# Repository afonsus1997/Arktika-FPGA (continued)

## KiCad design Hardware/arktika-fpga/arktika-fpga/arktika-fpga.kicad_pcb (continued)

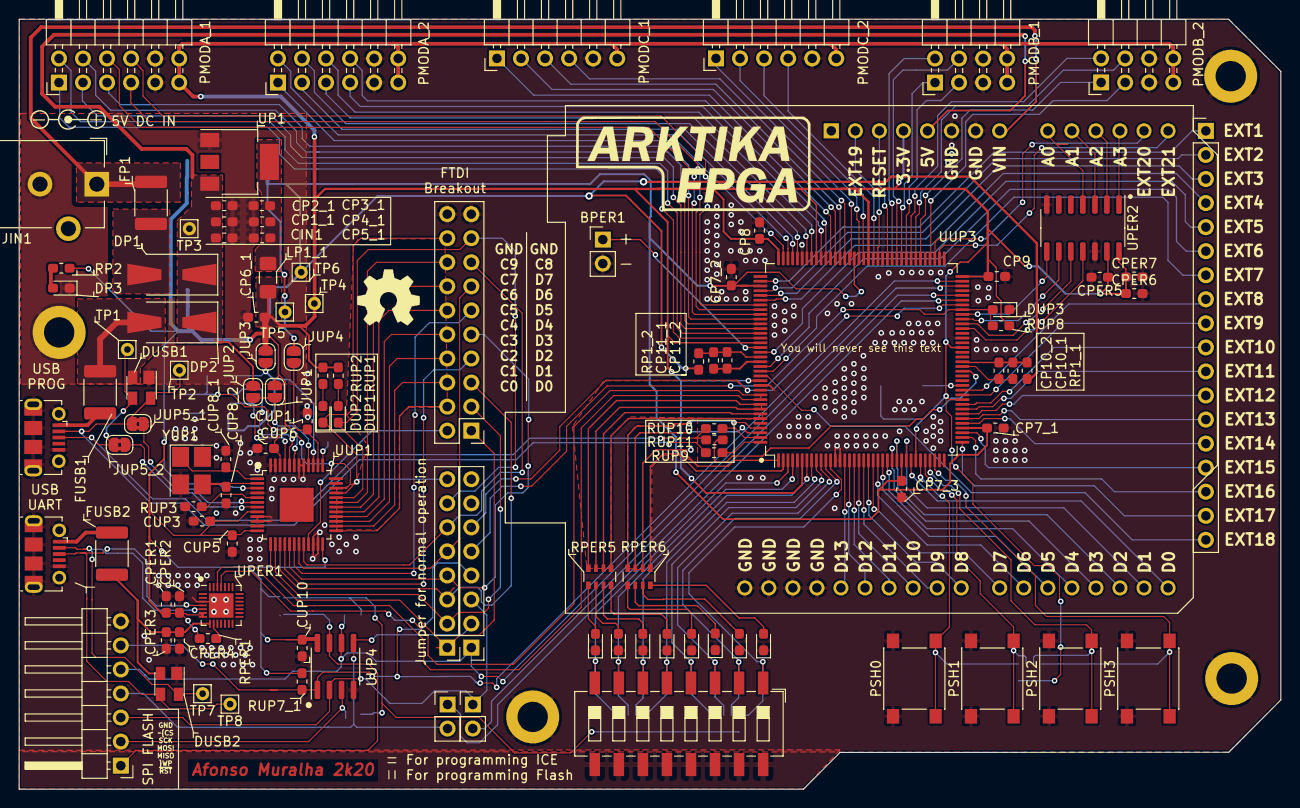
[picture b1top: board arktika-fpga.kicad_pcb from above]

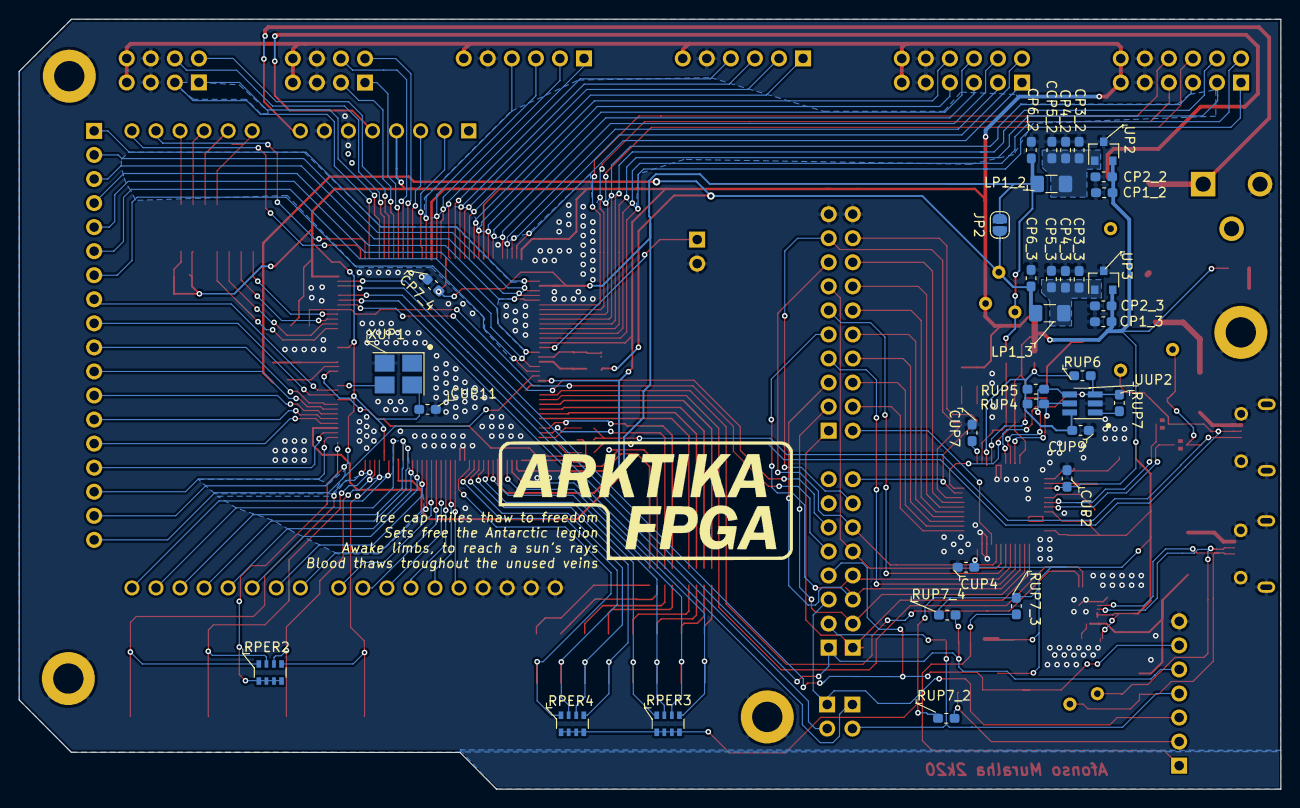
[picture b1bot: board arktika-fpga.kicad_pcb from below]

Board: 2 copper layers, 133.2 x 81.3 mm, 143 parts (35 on the bottom side), 178 nets.

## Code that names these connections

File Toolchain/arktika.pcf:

#Board Dedicated Oscillator
set_io --warn-no-port CLK 49

#=======Board LEDs========
set_io --warn-no-port LED0 2
set_io --warn-no-port LED1 1
set_io --warn-no-port LED2 142
set_io --warn-no-port LED3 141
set_io --warn-no-port LED4 139
set_io --warn-no-port LED5 138
set_io --warn-no-port LED6 137
set_io --warn-no-port LED7 136

set_io --warn-no-port led[0] 2
set_io --warn-no-port led[1] 1
set_io --warn-no-port led[2] 142
set_io --warn-no-port led[3] 141
set_io --warn-no-port led[4] 139
set_io --warn-no-port led[5] 138
set_io --warn-no-port led[6] 137
set_io --warn-no-port led[7] 136


#========Board Switches========
set_io --warn-no-port SW0 12
set_io --warn-no-port SW1 11
set_io --warn-no-port SW2 10
set_io --warn-no-port SW3 9
set_io --warn-no-port SW4 8
set_io --warn-no-port SW5 7
set_io --warn-no-port SW6 4
set_io --warn-no-port SW7 3

set_io --warn-no-port sw[0] 12
set_io --warn-no-port sw[1] 11
set_io --warn-no-port sw[2] 10
set_io --warn-no-port sw[3] 9
set_io --warn-no-port sw[4] 8
set_io --warn-no-port sw[5] 7
set_io --warn-no-port sw[6] 4
set_io --warn-no-port sw[7] 3


#========Board Push Buttons========
set_io --warn-no-port PSH0 31
set_io --warn-no-port PSH1 32
set_io --warn-no-port PSH2 33
set_io --warn-no-port PSH3 34

set_io --warn-no-port psh[0] 31
set_io --warn-no-port psh[1] 32
set_io --warn-no-port psh[2] 33
set_io --warn-no-port psh[3] 34

#========Board EXT Header========
set_io --warn-no-port EXT1 110
set_io --warn-no-port EXT2 112
set_io --warn-no-port EXT3 113
set_io --warn-no-port EXT4 114
set_io --warn-no-port EXT5 125
set_io --warn-no-port EXT6 128
set_io --warn-no-port EXT7 129
set_io --warn-no-port EXT8 48
set_io --warn-no-port EXT9 47
set_io --warn-no-port EXT10 45
set_io --warn-no-port EXT11 44
set_io --warn-no-port EXT12 43
set_io --warn-no-port EXT13 42
set_io --warn-no-port EXT14 41
set_io --warn-no-port EXT15 39
set_io --warn-no-port EXT16 38
set_io --warn-no-port EXT17 37
set_io --warn-no-port EXT18 130

 
#========Board Arduino Headers========
set_io --warn-no-port D0 29
set_io --warn-no-port D1 28
set_io --warn-no-port D2 26
set_io --warn-no-port D3 25
set_io --warn-no-port D4 24
set_io --warn-no-port D5 23
set_io --warn-no-port D6 22
set_io --warn-no-port D7 21
set_io --warn-no-port D8 20
set_io --warn-no-port D9 19
set_io --warn-no-port D10 18
set_io --warn-no-port D11 17
set_io --warn-no-port D12 16
set_io --warn-no-port D13 15

set_io --warn-no-port ARDUINO_RESET 85 
set_io --warn-no-port EXTRA1 87
set_io --warn-no-port EXTRA2 74
set_io --warn-no-port EXTRA3 75


#========Board Buzzer Header======== 
set_io --warn-no-port BUZZER 124 


#========Board ADC Pins========
set_io --warn-no-port ADC_CLK 61
set_io --warn-no-port ADC_MISO 62
set_io --warn-no-port ADC_MOSI 63
set_io --warn-no-port ADC_CS 64

#========Board USB Pins========
set_io --warn-no-port USBP 143
set_io --warn-no-port USBP2 52
set_io --warn-no-port USBN 144
set_io --warn-no-port UART_TX 135
set_io --warn-no-port UART_RX 134


#========Board PMOD Headers========
#TODO

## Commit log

2020-07-25 Updated to readme, initial hardware files
2020-07-25 Minor updates, added component search doc for development purposes
2020-07-25 Redid the kicad project. Last one was a mess
2020-07-25 Added more docs do readme, did board power
2020-07-26 Started doing usb and programming
2020-07-26 Added configuration for power regulation and programming nets
2020-07-26 Added misc components to the usb and prog schematic
2020-07-28 Added designators, some io, and some peripherals
2020-07-28 Assigned some footprints to components
2020-07-29 Minor fixes
2020-07-29 Minor fixes on fpga peripherals
2020-07-29 JNC: Updated component search doc with component list and datasheet links
2020-07-30 Minor fixes, added peripheral buses, added annotations and added crystal datasheets
2020-07-30 Added alternate power intput. Update some designators. Added fpga crystal
2020-07-30 Added fuse to usb peripheral, other minor changes
2020-07-30 Forgot to change fusb2 designator
2020-07-30 Updated eeprom info in component search, added missing bp cap to eeprom
2020-07-30 Misc changes and fixes
2020-07-31 Addded new hybrid crystal footprint, fixed missing footprints, created layout file for testing
2020-07-31 Added fuses library to project. Minor changes
2020-07-31 Added rescue files
2020-08-01 Misc schematic changes. Preliminary layout almost complete
2020-08-02 Major routing updates. Did work on silkscreen. Optimized io placing. Misc changes
2020-08-02 Added more IO
2020-08-02 Finished routing, did gnd planes, added more silkscreen and some manual via stitching. Pre-final layout.
2020-08-03 Minor layout fixes
2020-08-03 Fixed minor drc errors. removed usb jumpers and added needed resistors
2020-08-03 Minor layout changes
2020-08-04 Added silkscreen art and added media folder with the same art
2020-08-04 Minor layout fixes. Added new micro usb connector footprint and link. Misc silk changes
2020-08-04 Added pcbway logo to top silkscreen
2020-08-04 misc changes, exported test gerbers
2020-08-05 Exported final gerbers. Sent to fab
2020-08-06 Fixed clearance error on design. Sent to fab
2020-08-07 Fixed gerber format issue with manufacturer
2020-08-11 Added initial files for the toolchain information. Added basic example. Added pcf board file
2020-08-24 Generated gerbers without pcbway branding. Sent do fab
2020-09-22 exported schematics pdf
2020-09-27 Updated readme and added renders
2020-09-28 Fixed flash CS net
2020-09-28 Edited basic example and added a makefile and makefile template
